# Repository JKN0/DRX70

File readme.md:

# DRX70 - FM synthesizer module

DRX70 is an FM midi synthesizer module with 8 voice polyphony and 4 operators per voice. It includes also a sample based drum machine and built-in chorus effect. Sounds can be edited using local display and buttons, or via midi sysex. It has both traditional midi and USB midi interfaces. 

Synthesizer is modified from a Yamaha PSR-70 entry-level home keyboard from 1985, with small number of fixed sound presets and auto accompaniment. 

Modifications done:
- Keyboard has been modified to midi sound module by removing the main circuit boards and installing them to a new case
- New firmware for Yamaha boards has been written from scratch (the Z80 part)
- Another CPU has been added to handle new user interface and USB (the 8051 part)
- Sounds have been converted from similar synths, like DX100

This is a continuation project for https://github.com/JKN0/PSR70-reverse

Files:

- Boards: 
  - CPUinterface: adapter board for 8051 breakout
  - Pcomadapter: adapter board for communication between the two CPUs

- DRX_synth: synthesizer firmware for the Z80 part 

- DRX_ui: UI firmware for the 8051 part 

- Soundbanks: current soundbanks and conversion scripts

More details of the project: https://hackaday.io/project/207035-drx70-fm-synthesizer-module

Short sound demo: https://www.youtube.com/watch?v=fnx1b2eMlik

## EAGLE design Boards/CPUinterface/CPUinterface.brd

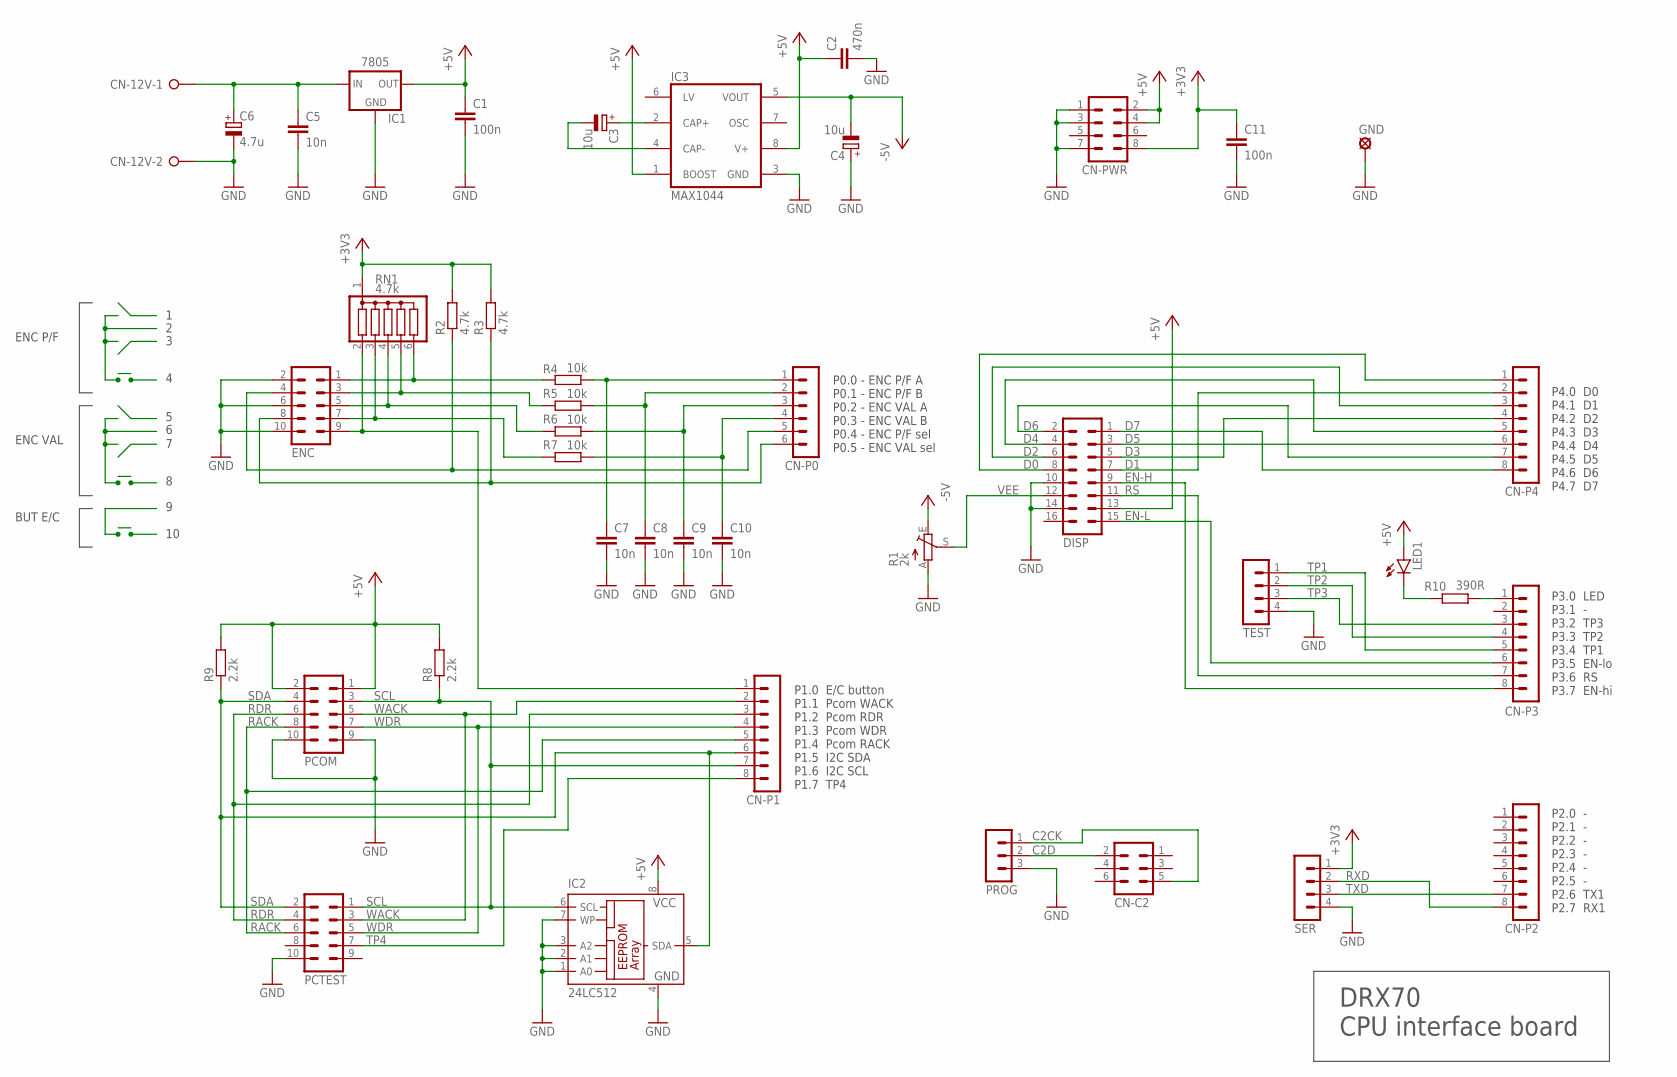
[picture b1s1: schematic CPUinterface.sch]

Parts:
C1, C11: 100n; C0805
C2: 470n; C0603
C3, C4: 10u; E2,5-6
C5, C7, C8, C9, C10: 10n; C0603
C6: 4.7u; SMC_A
CN-12V: W237-02P; W237-132
CN-C2: MA03-2
CN-P0: MA06-1
CN-P1, CN-P2, CN-P3, CN-P4: MA08-1
CN-PWR: MA04-2
DISP: MA08-2
ENC: MA05-2
GND: LSP10
IC1: 7805; 78XXL
IC2: 24LC512; SO-08
IC3: MAX1044; DIL08
LED1: LED3MM
PCOM: MA05-2
PCTEST: MA05-2
PROG: MA03-1
R1: 2k; S63X
R2, R3: 4.7k; R0805
R4, R5, R6, R7: 10k; R0805
R8, R9: 2.2k; R0805
R10: 390R; R0805
RN1: 4.7k; SIL6
SER: MA04-1
TEST: MA04-1

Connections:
+3V3: C11.1, CN-PWR.8, R2.2, R3.2, RN1.1, SER.1
+5V: C1.1, C2.1, CN-PWR.2, CN-PWR.4, DISP.13, IC1.OUT, IC2.8 (VCC), IC3.1 (BOOST), IC3.8 (V+), LED1.A, PCOM.1, PCOM.2, R8.2, R9.2
+12V: C5.1, C6.+, CN-12V.1, IC1.IN
-5V: C4.-, IC3.5 (VOUT), R1.E
C2CK: CN-C2.5, PROG.1
C2D: CN-C2.2, PROG.2
D0: CN-P4.1, DISP.8
D1: CN-P4.2, DISP.7
D2: CN-P4.3, DISP.6
D3: CN-P4.4, DISP.5
D4: CN-P4.5, DISP.4
D5: CN-P4.6, DISP.3
D6: CN-P4.7, DISP.2
D7: CN-P4.8, DISP.1
EN-H: CN-P3.8, DISP.9
EN-L: CN-P3.6, DISP.15
GND: C1.2, C2.2, C4.+, C5.2, C6.-, C7.2, C8.2, C9.2, C10.2, C11.2, CN-12V.2, CN-PWR.1, CN-PWR.3, CN-PWR.7, DISP.10, DISP.14, ENC.2, ENC.6, ENC.10, GND.MP, IC1.GND, IC2.1 (A0), IC2.2 (A1), IC2.3 (A2), IC2.4 (GND), IC2.7 (WP), IC3.3 (GND), PCOM.9, PCOM.10, PCTEST.10, PROG.3, R1.A, SER.4, TEST.4
unnamed: C3.+, IC3.2 (CAP+)
unnamed: C3.-, IC3.4 (CAP-)
unnamed: CN-P3.1, R10.1
unnamed: ENC.1, R4.2, RN1.6
unnamed: ENC.3, R5.2, RN1.5
unnamed: ENC.5, R6.2, RN1.4
unnamed: ENC.7, R7.2, RN1.3
unnamed: LED1.K (C), R10.2
unnamed: CN-P1.1, ENC.9, RN1.2
unnamed: C10.1, CN-P0.4, R7.1
unnamed: C9.1, CN-P0.3, R6.1
unnamed: C8.1, CN-P0.2, R5.1
unnamed: C7.1, CN-P0.1, R4.1
unnamed: CN-P0.6, ENC.8, R3.1
unnamed: CN-P0.5, ENC.4, R2.1
RACK: CN-P1.5, PCOM.8, PCTEST.6
RDR: CN-P1.3, PCOM.6, PCTEST.4
RS: CN-P3.7, DISP.11
RXD: CN-P2.8, SER.2
SCL: CN-P1.7, IC2.6 (SCL), PCOM.3, PCTEST.1, R8.1
SDA: CN-P1.6, IC2.5 (SDA), PCOM.4, PCTEST.2, R9.1
TP1: CN-P3.5, TEST.1
TP2: CN-P3.4, TEST.2
TP3: CN-P3.3, TEST.3
TP4: CN-P1.8, PCTEST.7
TXD: CN-P2.7, SER.3
VEE: DISP.12, R1.S
WACK: CN-P1.2, PCOM.5, PCTEST.3
WDR: CN-P1.4, PCOM.7, PCTEST.5

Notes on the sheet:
ENC P/F
ENC VAL
BUT E/C
P0.0 - ENC P/F A P0.1 - ENC P/F B P0.2 - ENC VAL A P0.3 - ENC VAL B P0.4 - ENC P/F sel P0.5 - ENC VAL sel
P1.0 E/C button P1.1 Pcom WACK P1.2 Pcom RDR P1.3 Pcom WDR P1.4 Pcom RACK P1.5 I2C SDA P1.6 I2C SCL P1.7 TP4
P4.0 D0 P4.1 D1 P4.2 D2 P4.3 D3 P4.4 D4 P4.5 D5 P4.6 D6 P4.7 D7
P3.0 LED P3.1 - P3.2 TP3 P3.3 TP2 P3.4 TP1 P3.5 EN-lo P3.6 RS P3.7 EN-hi
P2.0 - P2.1 - P2.2 - P2.3 - P2.4 - P2.5 - P2.6 TX1 P2.7 RX1
DRX70 CPU interface board

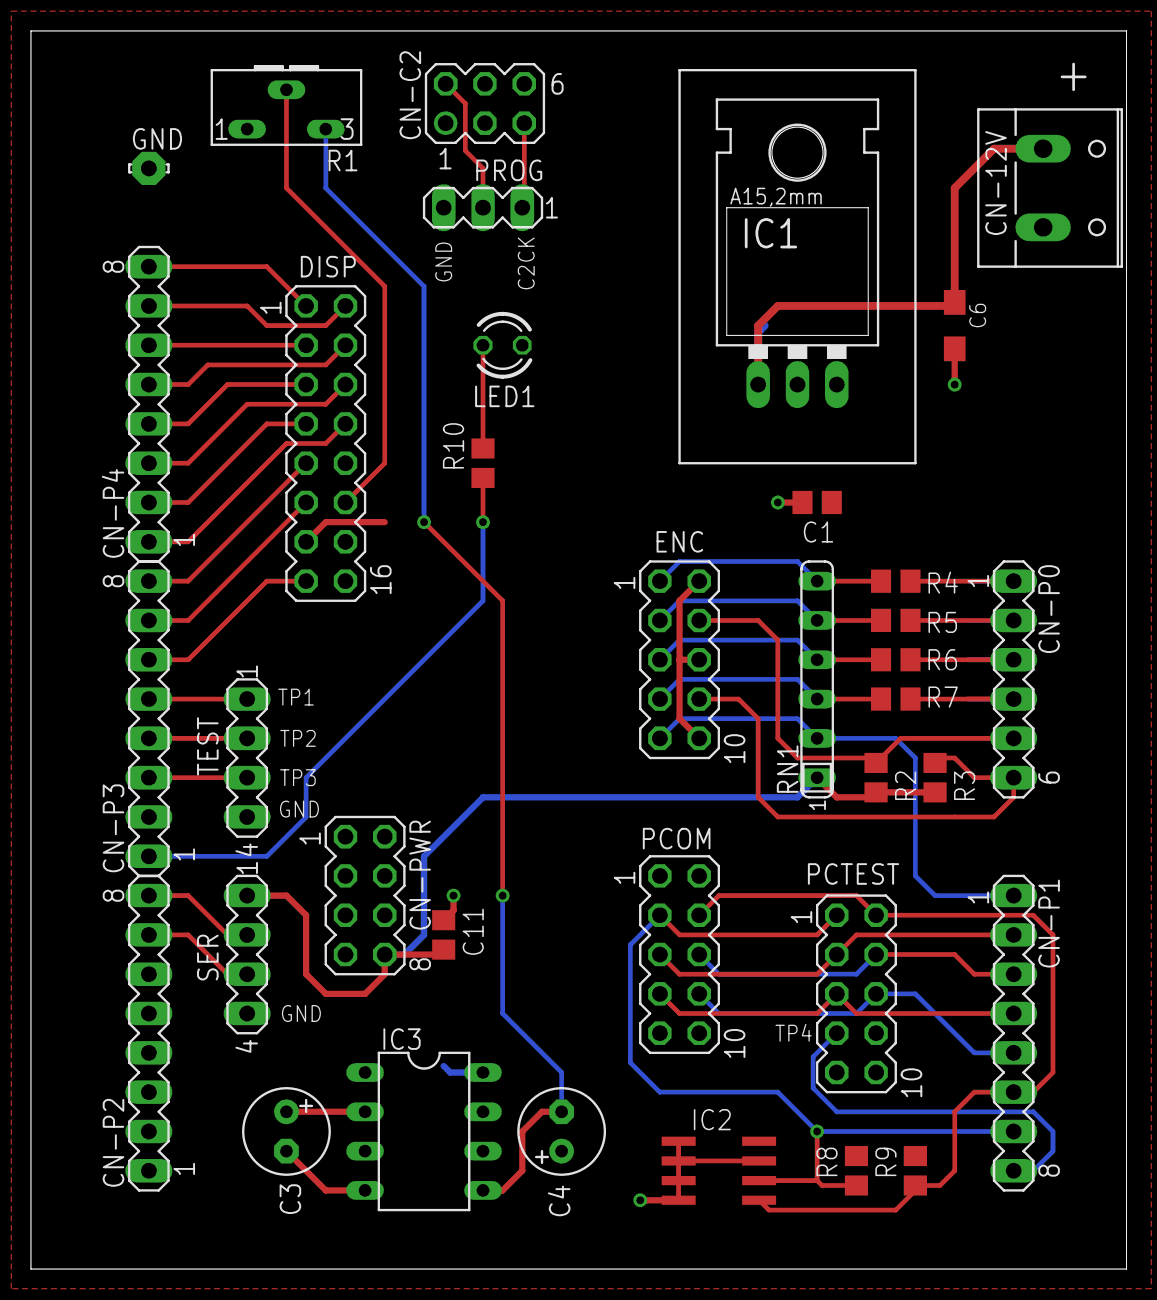
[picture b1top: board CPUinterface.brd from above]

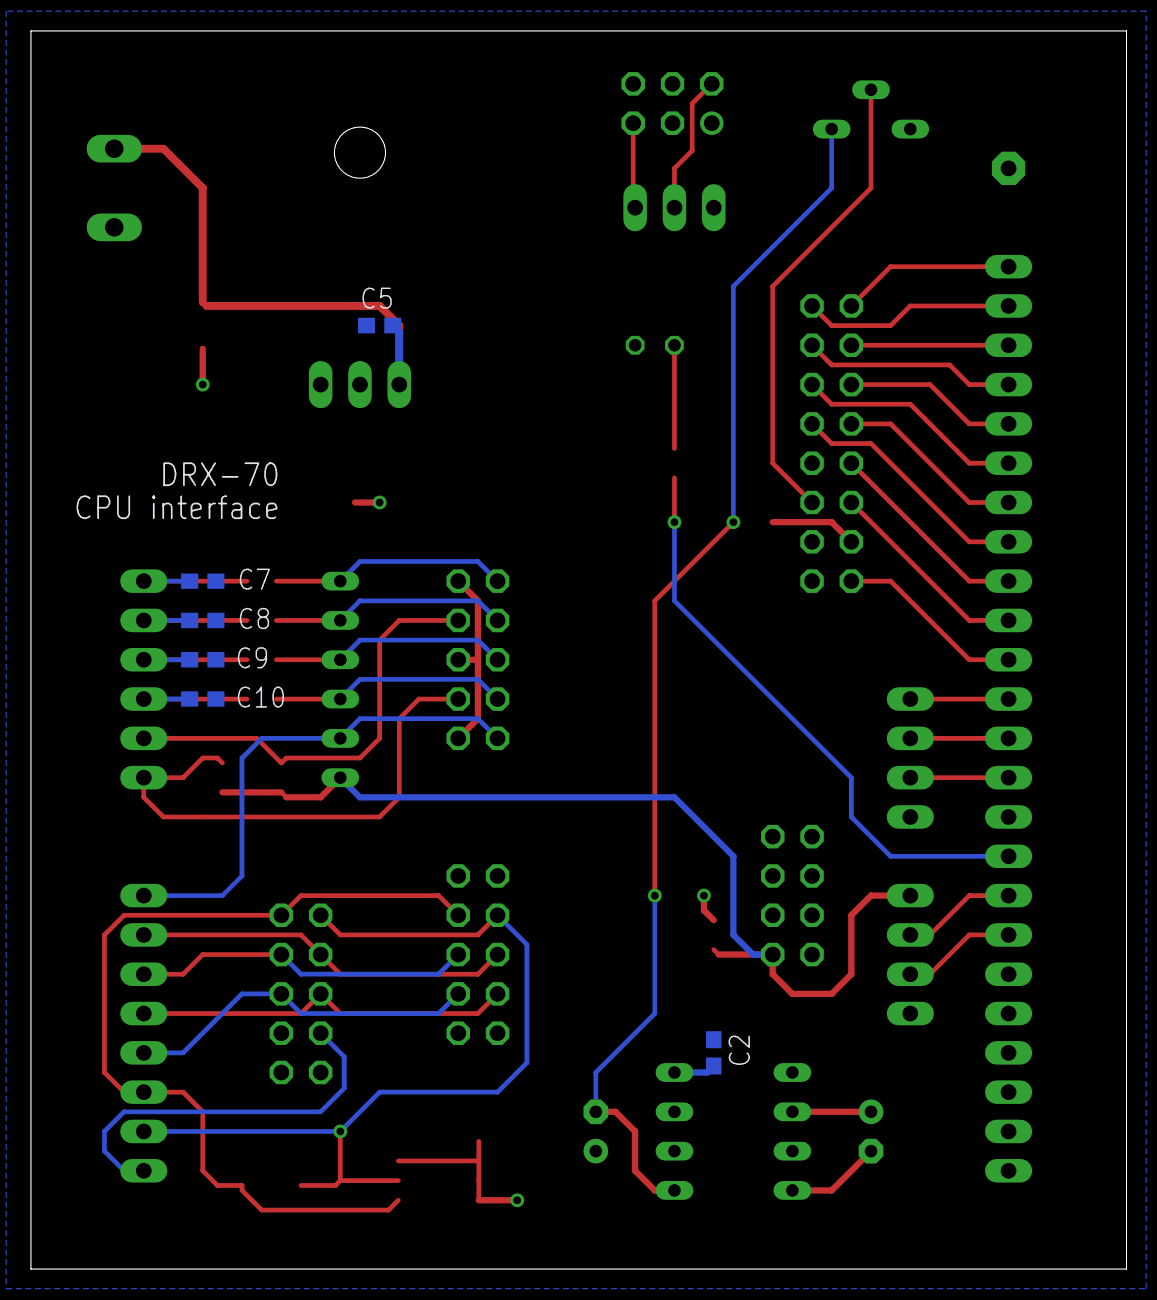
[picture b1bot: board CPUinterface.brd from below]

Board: 2 copper layers, 70.8 x 80.0 mm, 42 parts (6 on the bottom side), 46 nets.

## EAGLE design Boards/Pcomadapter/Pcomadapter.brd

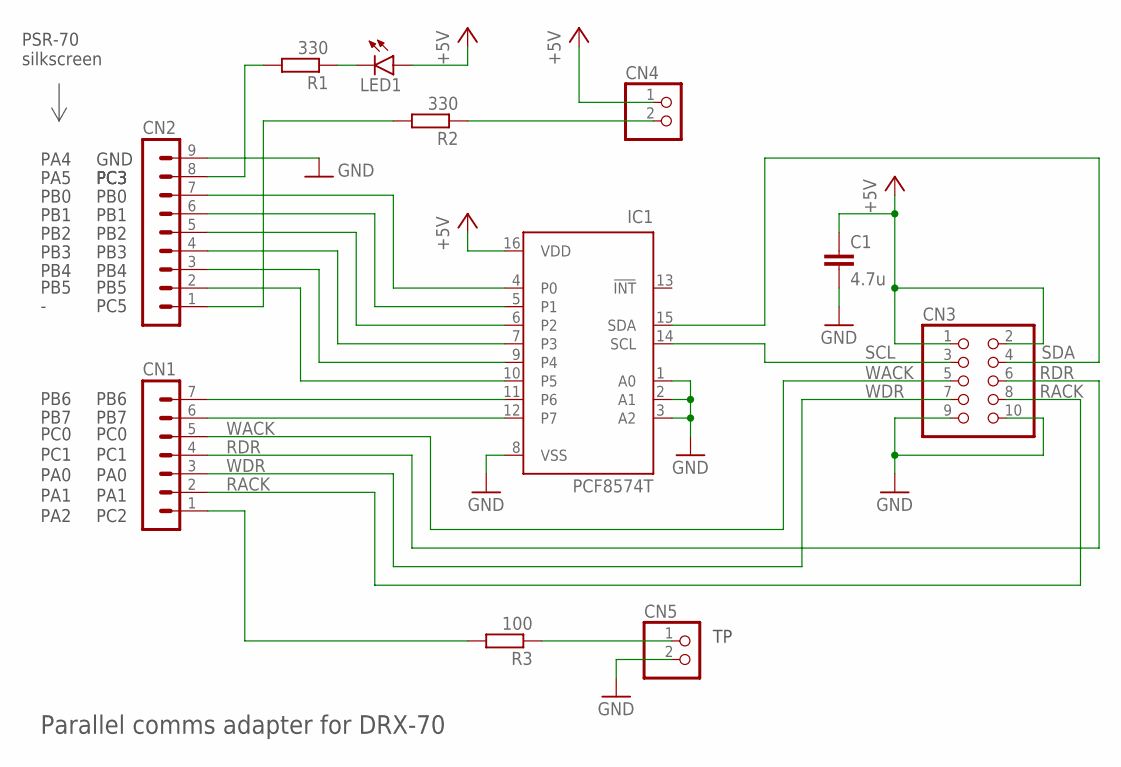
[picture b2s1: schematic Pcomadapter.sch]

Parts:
C1: 4.7u; C0805
CN1: MA07-1
CN2: MA09-1
CN3: PINHD-2X5/90; 2X05/90
CN4, CN5: PINHD-1X2/90; 1X02/90
IC1: PCF8574T; SO16W
LED1: LED3MM
R1, R2: 330; R0805
R3: 100; R0805

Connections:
+5V: C1.1, CN3.1, CN3.2, CN4.1, IC1.16 (VDD), LED1.A
GND: C1.2, CN2.9, CN3.9, CN3.10, CN5.2, IC1.1 (A0), IC1.2 (A1), IC1.3 (A2), IC1.8 (VSS)
unnamed: CN2.7, IC1.4 (P0)
unnamed: CN2.6, IC1.5 (P1)
unnamed: CN2.5, IC1.6 (P2)
unnamed: CN2.4, IC1.7 (P3)
unnamed: CN2.3, IC1.9 (P4)
unnamed: CN2.2, IC1.10 (P5)
unnamed: CN1.7, IC1.11 (P6)
unnamed: CN1.6, IC1.12 (P7)
unnamed: CN1.1, R3.2
unnamed: CN5.1, R3.1
unnamed: CN2.8, R1.2
unnamed: LED1.K (C), R1.1
unnamed: CN2.1, R2.2
unnamed: CN4.2, R2.1
RACK: CN1.2, CN3.8
RDR: CN1.4, CN3.6
SCL: CN3.3, IC1.14 (SCL)
SDA: CN3.4, IC1.15 (SDA)
WACK: CN1.5, CN3.5
WDR: CN1.3, CN3.7

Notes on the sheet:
PC3
PC5
PC0
PC1
PB0
PB1
PB2
PB3
PB4
PB5
PB6
PB7
PA0
PA1
PA5
PSR-70 silkscreen
Parallel comms adapter for DRX-70
PA4
GND
PC2
PA2

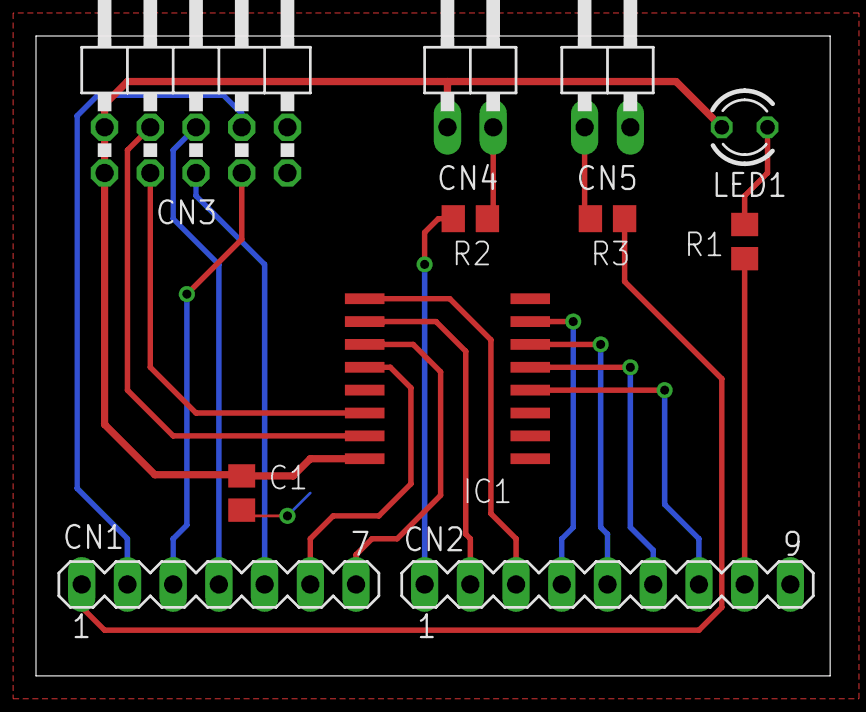
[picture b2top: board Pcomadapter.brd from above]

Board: 2 copper layers, 44.1 x 35.5 mm, 11 parts (0 on the bottom side), 22 nets.

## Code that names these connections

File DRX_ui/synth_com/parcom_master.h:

/***************************************************************************
 
 parcom_master.h
 
 Master for DRX-70 internal parallel port communication
 
 5.9.2021

 ***************************************************************************/

/* --------------------------------------------------------------------------
 
 Usage from main program:
 
 - #include "parcom_slave.h"
 - call PC_init()
 - main loop: call PC_run_tasks()
 
 - sending data to master (when master has requested):
    - PC_send_to_slave()
    - sending is ready, when PC_comm_busy() returns false
 - receiving data from master:
    - command reading with PC_send_to_slave()
    - data available, when PC_get_rx_buf() returns != NULL
    - data is in the returned buffer
    - buffer is acknowledged by calling PC_ack_rx()

 ---------------------------------------------------------------------------- */

/* =====================================================================
------------------------ Constants & macros ------------------------- */

#ifndef _PARCOM_MASTER_H_
#define _PARCOM_MASTER_H_

#ifndef FALSE
#define FALSE               0
#endif

#ifndef TRUE
#define TRUE                1
#endif

#define MSGBUF_LEN          40      // ring buffer len in structs (40*4 bytes)
#define PCBUF_LEN           150

#define RTC_TIME            5
#define TX_TIMEOUT          (200/RTC_TIME)
#define RX_TIMEOUT          (200/RTC_TIME)

extern BIT pc_error;

/* =======================================================================
------------------------ I/O ------------------------------------------ */

#define WDR                  P1_3       // Write Data Ready (out)
#define WACK                 P1_1       // Write Ack        (in)
#define RDR                  P1_2       // Read Data Ready  (in)
#define RACK                 P1_4       // Read Ack         (out)

#define CMD_WRITE            0x00
#define CMD_READ             0x80
#define CMD_NONE             0xFF

/* =======================================================================
----------------------------------------------------------------------- */

void PC_init( void );
void PC_send_patch_to_synth( void ) __reentrant;
void PC_send_drumkit_to_synth( void ) __reentrant;
void PC_send_settings_to_synth( void ) __reentrant;
void PC_send_byte_param_to_synth( BYTE scmd, BYTE op_inst, BYTE parval ) __reentrant;
void PC_send_word_param_to_synth( BYTE scmd, BYTE op_inst, WORD parval ) __reentrant;
void PC_send_midi_msg_to_synth( XDATA BYTE *midibuf, BYTE len ) __reentrant;
BIT PC_comm_busy( void );
XDATA BYTE *PC_get_rx_buf( BYTE *len );
void PC_ack_rx( void );
void PC_update_timeouts( void )  __using (1);
void PC_run_tasks( void );

#endif

/* ============================ EOF ====================================== */
